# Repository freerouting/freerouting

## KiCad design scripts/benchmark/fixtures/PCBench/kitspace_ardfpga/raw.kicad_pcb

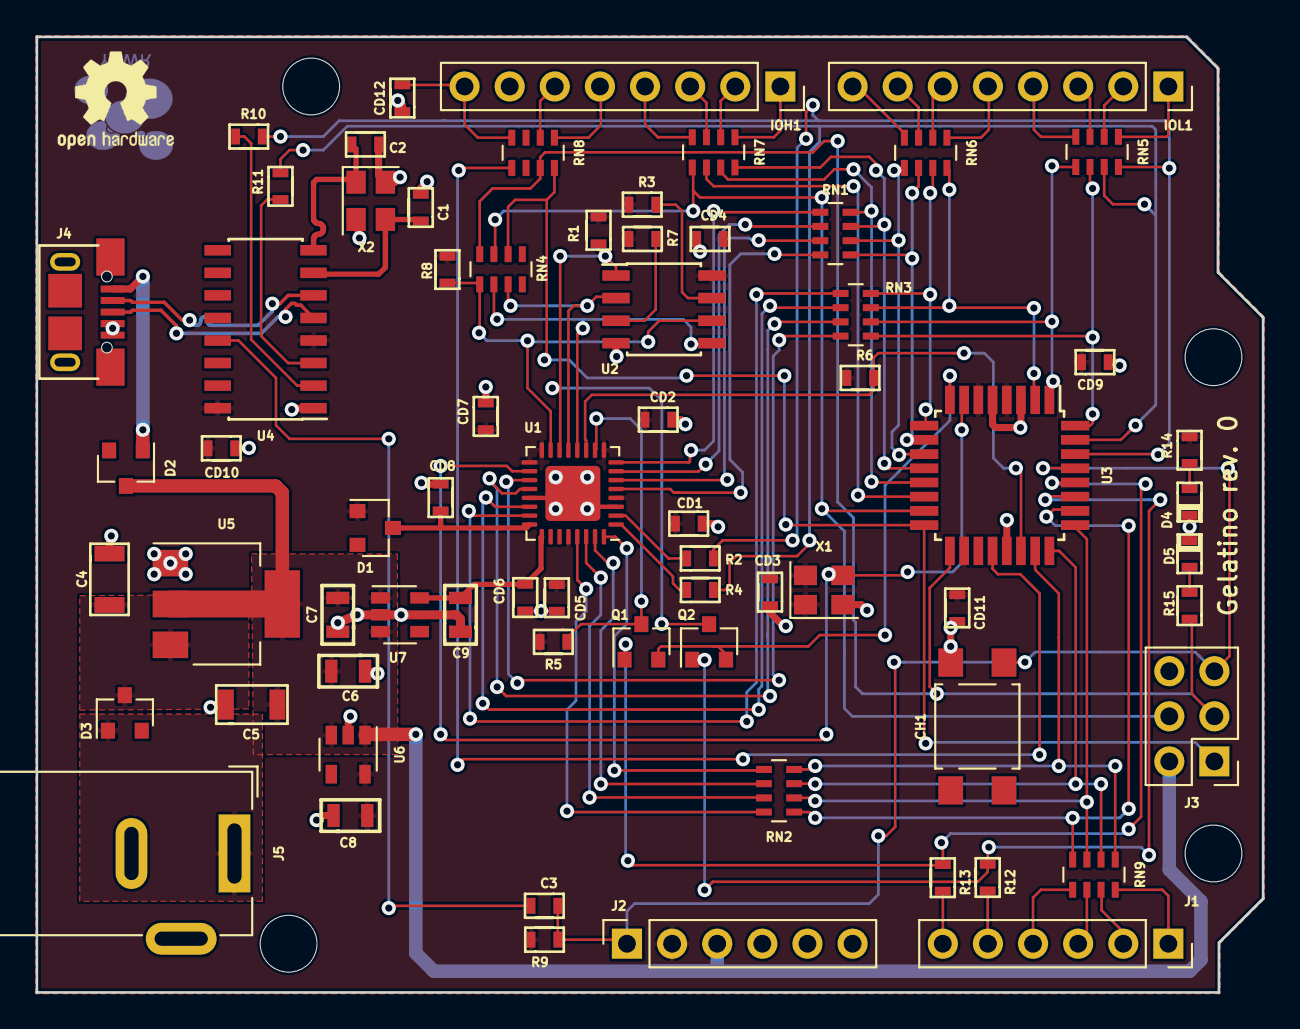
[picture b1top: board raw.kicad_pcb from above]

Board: 2 copper layers, 69.0 x 53.8 mm, 69 parts (0 on the bottom side), 84 nets.

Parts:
C1, C2: 33pF; 0603_CAP
C3: 100nF; 0603_CAP
C4, C5: 10uF; 1206_SMD
C6, C7, C8, C9: 1uF; 0805_SMD
CD1, CD2, CD3, CD4, CD5, CD6, CD7, CD8, CD9, CD10, CD11, CD12: 100nF; 0603_CAP
CH1: RESET; SW_SPST_TL3305A
D1, D2, D3: D_Schottky_Small_ALT; SOT-23
D4, D5: LED_Small_ALT; 0603_LED
IOH1: Conn_01x08; PinSocket_1x08_P2.54mm_Vertical
IOL1: Conn_01x08; PinSocket_1x08_P2.54mm_Vertical
J1: AD; PinSocket_1x06_P2.54mm_Vertical
J2: PWR; PinSocket_1x06_P2.54mm_Vertical
J3: ICSP; PinHeader_2x03_P2.54mm_Vertical
J4: USB; USB-Micro-LCSC
J5: POWER; BarrelJack_Wuerth_6941xx301002
Q1, Q2: NMOS; SOT-23
R1, R3, R5, R6, R7, R8, R9: 10k; 0603_RES
R2, R4: 100; 0603_RES
R10, R11, R12, R13: 1k; 0603_RES
R14, R15: 220; 0603_RES
RN1, RN2, RN3, RN4: 100; R_Array_Concave_4x0603
RN5, RN6, RN7, RN8, RN9: 1k; R_Array_Concave_4x0603
U1: iCE40LP384; QFN-32-1EP_5x5mm_P0.5mm_EP3.1x3.1mm
U2: AT25xxx; SOIC-8_3.9x4.9mm_P1.27mm
U3: ATMega328; TQFP-32_7x7mm_P0.8mm
U4: CH340G; SOIC-16_3.9x9.9mm_P1.27mm
U5: AMS1117-5.0; SOT-223-3_TabPin2
U6: RT9013-33; SOT-23-5
U7: RT9013-12; SOT-23-5
X1: 16MHz; Oscillator_SMD_Abracon_ASE-4Pin_3.2x2.5mm
X2: 12 MHz; Oscillator_SMD_Abracon_ASE-4Pin_3.2x2.5mm

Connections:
+1.2V: C9.1, CD6.1, U1.25, U7.5
+3.3V: C8.1, CD1.1, CD2.1, CD3.1, CD4.1, CD5.1, CD7.1, CD9.2, CD10.1, CD11.1, D1.1, J2.2, R1.1, R3.1, R5.1, R6.1, R7.2, R8.1, R9.2, R14.2, U1.4, U1.9, U1.16, U1.17, U1.28, U2.8, U3.4, U3.6, U3.18, U4.4, U4.16, U6.5, X1.1, X1.4
+5V: C5.1, C6.1, C7.1, D2.3, J2.3, J3.2, U5.2, U6.1, U6.3, U7.1, U7.3
AD0: RN2.4, RN9.1, U3.23
AD1: RN2.3, RN9.2, U3.24
AD2: RN2.2, RN9.3, U3.25
AD3: RN2.1, RN9.4, U3.26
AD4: Q2.G, R12.1, U3.27
AD5: Q1.G, R13.1, U3.28
AREF: RN8.5, U3.20
CLK16: U1.18, U3.7, X1.3
DONE: R6.2, U1.11, U3.22
DTR: C3.1, U4.13
FRST: Q1.D, R5.2, U1.10
FSCK: R8.2, RN4.1, U1.15, U2.6
FSDI: RN4.3, U1.13, U2.2
FSDO: RN4.2, U1.12, U2.5
FSEL: Q1.S, Q2.S, U3.8
FSS: Q2.D, R1.2, U1.14, U2.1
GND: C1.1, C2.1, C4.2, C5.2, C6.2, C7.2, C8.2, C9.2, CD1.2, CD2.2, CD3.2, CD4.2, CD5.2, CD6.2, CD7.2, CD8.2, CD9.1, CD10.2, CD11.2, CD12.2, CH1.1, D4.1, D5.1, IOH1.7, J2.4, J2.5, J3.6, J4.4, J4.5, J5.2, U1.3, U1.21, U1.33, U2.4, U3.3, U3.5, U3.21, U4.1, U5.1, U6.2, U7.2, X1.2, X2.0
IO0: R2.1, R10.2, RN5.8, U3.30
IO1: R4.1, R11.2, RN5.7, U3.31
IO2: RN3.5, RN5.6, U3.32
IO3: RN3.6, RN5.5, U3.1
IO4: RN3.7, RN6.8, U3.2
IO5: RN3.8, RN6.7, U3.9
IO6: RN1.1, RN6.6, U3.10
IO7: RN1.2, RN6.5, U3.11
IO8: RN1.3, RN7.8, U3.12
IO9: RN1.4, RN7.7, U3.13
MRST: C3.2, CH1.2, J2.1, J3.5, R9.1, U3.29
MSCK: J3.3, R15.2, RN4.8, RN8.7, U3.17
MSDI: J3.1, RN4.6, RN8.8, U3.16
MSDO: J3.4, RN4.7, RN7.5, U3.15
MSS: RN7.6, U3.14
unnamed: C1.2, U4.7, X2.2
unnamed: C2.2, U4.8, X2.1
unnamed: CD8.1, D1.3, U1.24
unnamed: CD12.1, IOH1.8, RN8.4
unnamed: D2.1, J4.1
unnamed: D3.1, J5.1
unnamed: D4.2, R14.1
unnamed: D5.2, R15.1
unnamed: IOH1.1, RN7.1
unnamed: IOH1.2, RN7.2
unnamed: IOH1.3, RN7.3
unnamed: IOH1.4, RN7.4
unnamed: IOH1.5, RN8.1
unnamed: IOH1.6, RN8.2
unnamed: IOL1.1, RN5.1
unnamed: IOL1.2, RN5.2
unnamed: IOL1.3, RN5.3
unnamed: IOL1.4, RN5.4
unnamed: IOL1.5, RN6.1
unnamed: IOL1.6, RN6.2
unnamed: IOL1.7, RN6.3
unnamed: IOL1.8, RN6.4
unnamed: J1.1, RN9.8
unnamed: J1.2, RN9.7
unnamed: J1.3, RN9.6
unnamed: J1.4, RN9.5
unnamed: J1.5, R12.2
unnamed: J1.6, R13.2
unnamed: R2.2, U1.2
unnamed: R3.2, U2.7
unnamed: R4.2, U1.1
unnamed: R7.1, U2.3
unnamed: R10.1, U4.2
unnamed: R11.1, U4.3
unnamed: RN1.5, U1.8
unnamed: RN1.6, U1.7
unnamed: RN1.7, U1.6
unnamed: RN1.8, U1.5
unnamed: RN2.5, U1.32
unnamed: RN2.6, U1.31
unnamed: RN2.7, U1.30
unnamed: RN2.8, U1.29
unnamed: RN3.1, U1.23
unnamed: RN3.2, U1.22
unnamed: RN3.3, U1.20
unnamed: RN3.4, U1.19
USB_D+: J4.3, U4.5
USB_D-: J4.2, U4.6
V+: C4.1, D3.3, U5.3

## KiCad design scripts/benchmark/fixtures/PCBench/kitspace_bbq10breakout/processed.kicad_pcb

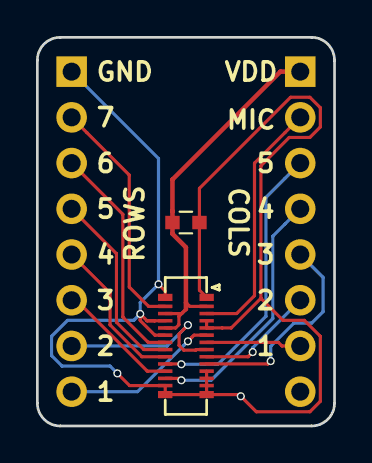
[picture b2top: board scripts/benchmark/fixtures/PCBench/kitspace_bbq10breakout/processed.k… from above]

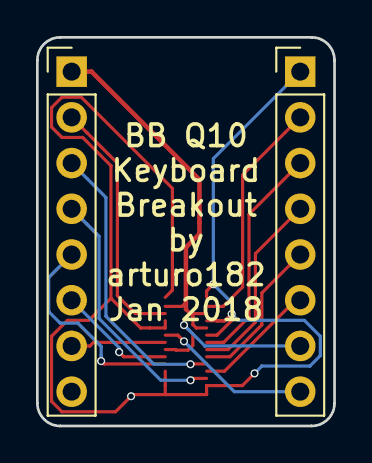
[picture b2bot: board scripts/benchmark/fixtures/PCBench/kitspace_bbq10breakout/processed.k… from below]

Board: 2 copper layers, 16.5 x 21.6 mm, 4 parts (2 on the bottom side), 15 nets.

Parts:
C1: 100uF; C_0603
J1, J2: Conn_01x08; Pin_Header_Straight_1x08_Pitch2.54mm
U1: BBQ10KBD; BM14B(0.8)-24DS-0.4V(53)

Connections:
/COL1: J2.7, U1.7
/COL2: J2.6, U1.9
/COL3: J2.5, U1.10
/COL4: J2.4, U1.17
/COL5: J2.3, U1.19
/MIC: J2.2, U1.3
/ROW1: J1.8, U1.6
/ROW2: J1.7, U1.8
/ROW3: J1.6, U1.18
/ROW4: J1.5, U1.20
/ROW5: J1.4, U1.21
/ROW6: J1.3, U1.22
/ROW7: J1.2, U1.27
GND: C1.2, J1.1, U1.1, U1.4, U1.5, U1.11, U1.12, U1.13, U1.14, U1.15, U1.16, U1.23, U1.25, U1.28
VDD: C1.1, J2.1, U1.2, U1.24, U1.26

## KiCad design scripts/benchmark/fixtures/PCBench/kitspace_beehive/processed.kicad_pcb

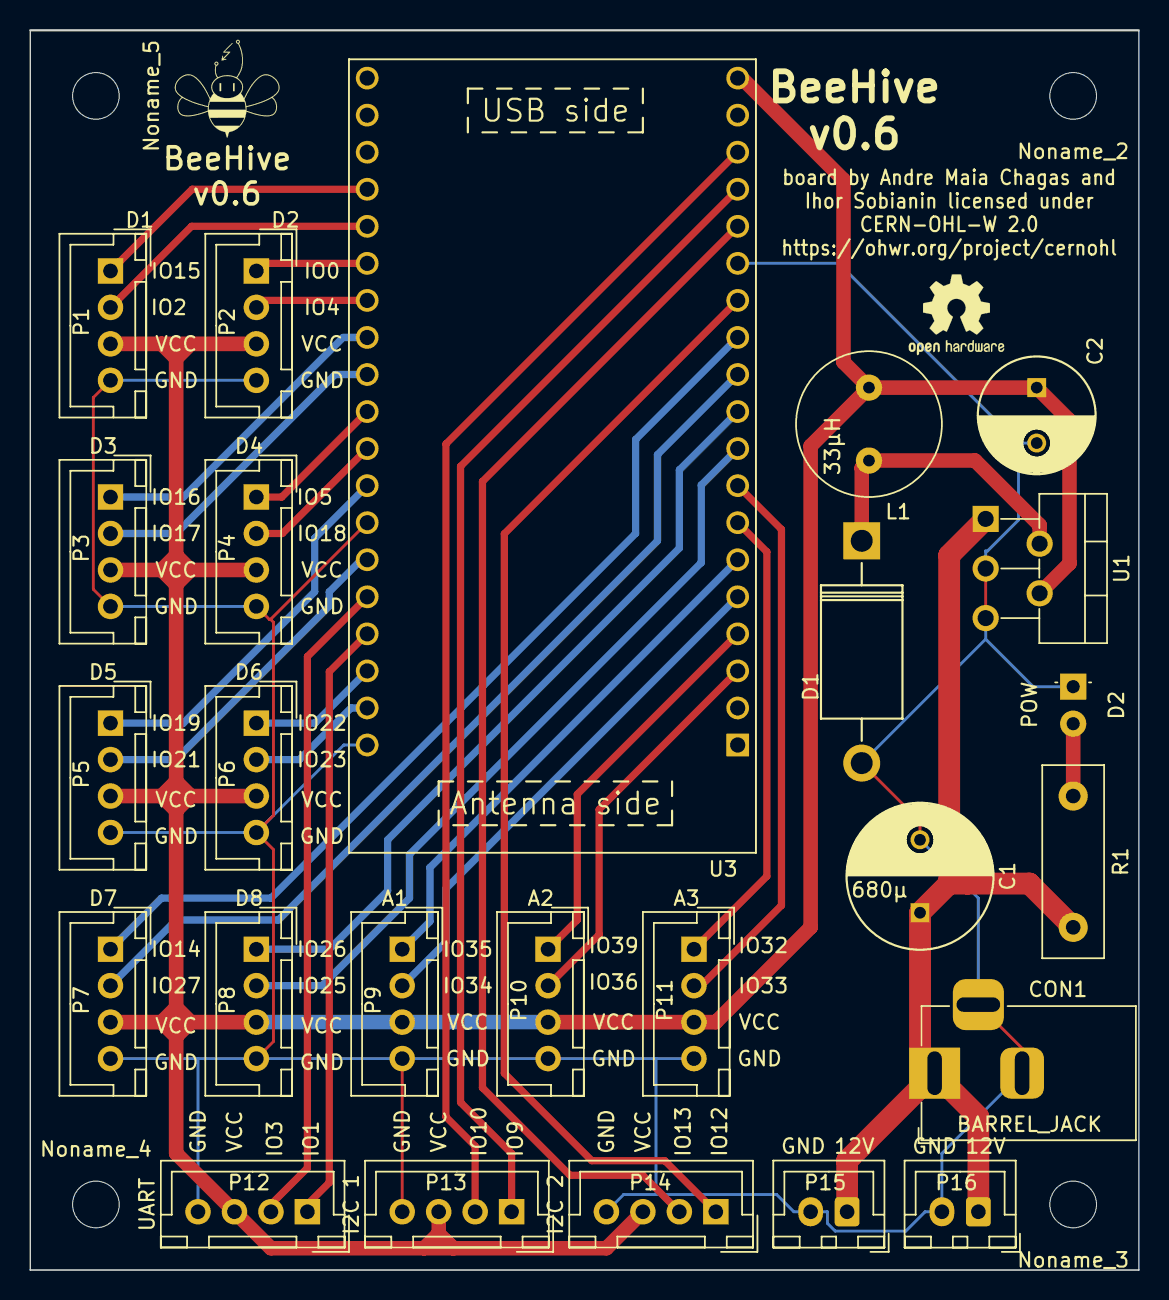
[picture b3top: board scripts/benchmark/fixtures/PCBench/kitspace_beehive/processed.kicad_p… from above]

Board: 2 copper layers, 76.0 x 85.0 mm, 31 parts (0 on the bottom side), 33 nets.

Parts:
C1: 680µ; C_Radial_D10_L21_P5
C2: 220µ; C_Radial_D8_L13_P3.8
CON1: BARREL_JACK; BarrelJack_Horizontal
D1: Schottky 5A; Diode_DO-201AD_Horizontal_RM15
D2: LED; LED_D3.0mm
L1: 33µH; Neosid_Inductor_MA-Bs75
Noname_1: (no value)
Noname_2, Noname_3, Noname_4, Noname_5: MountingHole_3.2mm_M3_DIN965
None_1: OSHW-Logo2_7.3x6mm_SilkScreen
P1: D1; JST_XH_B04B-XH-A_04x2.50mm_Straight
P2: D2; JST_XH_B04B-XH-A_04x2.50mm_Straight
P3: D3; JST_XH_B04B-XH-A_04x2.50mm_Straight
P4: D4; JST_XH_B04B-XH-A_04x2.50mm_Straight
P5: D5; JST_XH_B04B-XH-A_04x2.50mm_Straight
P6: D6; JST_XH_B04B-XH-A_04x2.50mm_Straight
P7: D7; JST_XH_B04B-XH-A_04x2.50mm_Straight
P8: D8; JST_XH_B04B-XH-A_04x2.50mm_Straight
P9: A1; JST_XH_B04B-XH-A_04x2.50mm_Straight
P10: A2; JST_XH_B04B-XH-A_04x2.50mm_Straight
P11: A3; JST_XH_B04B-XH-A_04x2.50mm_Straight
P12: UART; JST_XH_B04B-XH-A_04x2.50mm_Straight
P13: I2C 1; JST_XH_B04B-XH-A_04x2.50mm_Straight
P14: I2C 2; JST_XH_B04B-XH-A_04x2.50mm_Straight
P15, P16: Conn_01x02; JST_XH_B2B-XH-A_1x02_P2.50mm_Vertical
R1: 560; R_Box_L13.0mm_W4.0mm_P9.00mm
U1: LM2596T-5; TO-220-5_P3.4x3.7mm_StaggerOdd_Lead3.8mm_Vertical
U3: ESP32-DEVKITC-32D; MODULE_ESP32-DEVKITC-32D

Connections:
+5V: C2.1, L1.2, P1.3, P2.3, P3.3, P4.3, P5.3, P6.3, P7.3, P8.3, P9.3, P10.3, P11.3, P12.3, P13.3, P14.3, U1.4, U3.19
A1-3: P9.1, U3.6
A1-4: P9.2, U3.5
A2-3: P10.1, U3.4
A2-4: P10.2, U3.3
A3-3: P11.1, U3.7
A3-4: P11.2, U3.8
D1-3: P1.1, U3.35
D1-4: P1.2, U3.34
D2-3: P2.1, U3.33
D2-4: P2.2, U3.32
D3-3: P3.1, U3.31
D3-4: P3.2, U3.30
D4-3: P4.1, U3.29
D4-4: P4.2, U3.28
D5-3: P5.1, U3.27
D5-4: P5.2, U3.25
D6-3: P6.1, U3.22
D6-4: P6.2, U3.21
D7-3: P7.1, U3.12
D7-4: P7.2, U3.11
D8-3: P8.1, U3.10
D8-4: P8.2, U3.9
GND: C1.2, C2.2, CON1.2, CON1.3, D1.2, D2.1, P1.4, P2.4, P3.4, P4.4, P5.4, P6.4, P7.4, P8.4, P9.4, P10.4, P11.4, P12.4, P13.4, P14.4, P15.2, P16.2, U1.3, U1.5, U3.14, U3.20, U3.26
I2C_1-3: P13.1, U3.16
I2C_1-4: P13.2, U3.17
I2C_2-3: P14.1, U3.13
I2C_2-4: P14.2, U3.15
unnamed: C1.1, CON1.1, P15.1, P16.1, R1.2, U1.1
unnamed: D1.1, L1.1, U1.2
unnamed: D2.2, R1.1
RX: P12.2, U3.24
TX: P12.1, U3.23

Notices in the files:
scripts/benchmark/fixtures/PCBench/kitspace_beehive/processed.kicad_pcb:
board by Andre Maia Chagas and
Ihor Sobianin licensed under
CERN-OHL-W 2.0
